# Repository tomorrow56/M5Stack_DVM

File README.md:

# M5Stack_DVM

M5Stackの内蔵ADCで作るアナログ電圧計です。
M5StackのWi-Fi機能を使って、内蔵A-Dコンバータで測定したデータを電圧に変換してGoogleスプレッドシートに記録するexampleを追加しました。

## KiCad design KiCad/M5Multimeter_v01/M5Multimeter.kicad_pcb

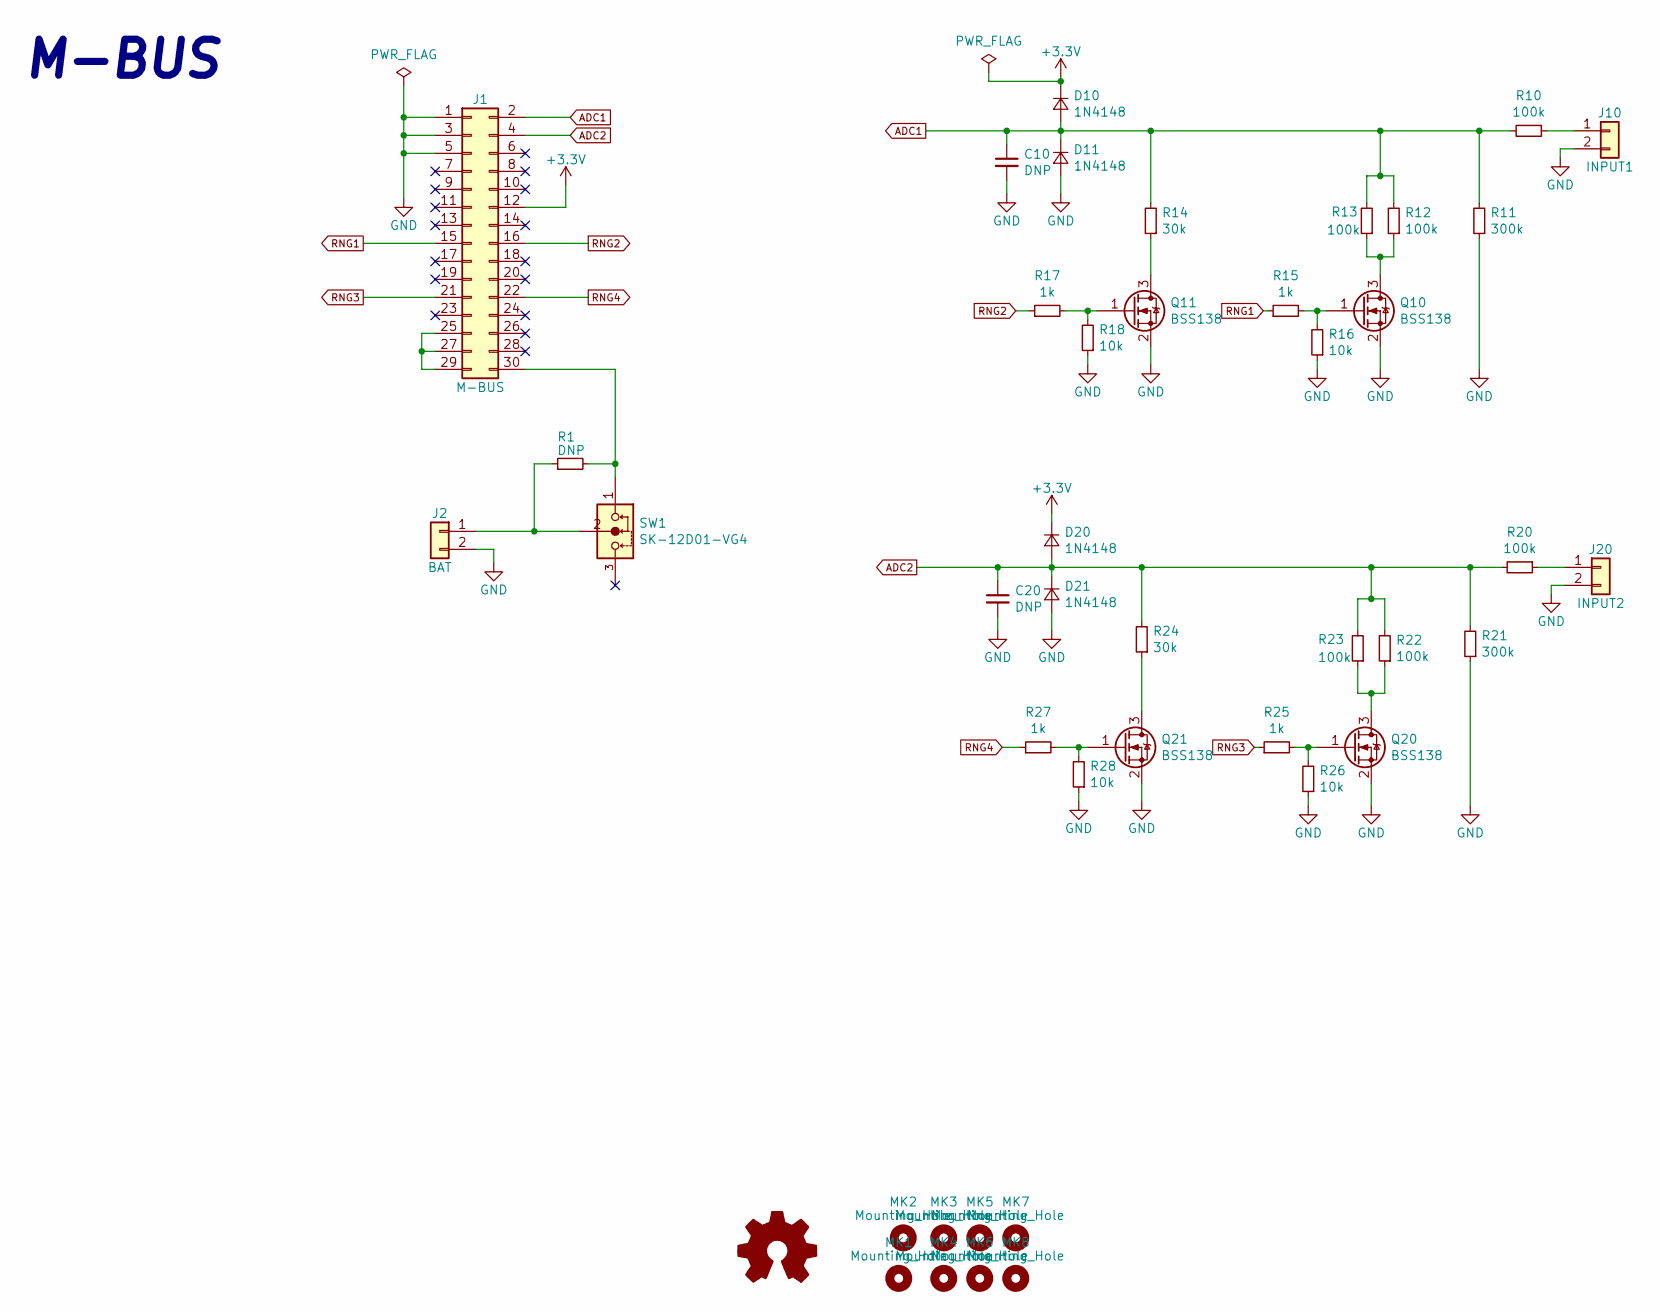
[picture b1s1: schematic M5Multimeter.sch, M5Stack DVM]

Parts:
C10, C20: DNP; C_0603
D10, D11, D20, D21: 1N4148; D_SOD-323
J1: M-BUS; Pin_Header_MBUS_SMD_TH
J2: BAT; Pin_Header_Angled_1x02_Pitch2.54mm
J10: INPUT1; Pin_Header_Angled_1x02_Pitch2.54mm
J20: INPUT2; Pin_Header_Angled_1x02_Pitch2.54mm
MK1, MK2, MK3, MK4: Mounting_Hole; MountingHole_3.2mm_M3
MK5, MK6, MK7, MK8: Mounting_Hole; MountingHole_2.2mm_M2
Q10, Q11, Q20, Q21: BSS138; SOT-23
R1: DNP; R_0603
R10, R12, R13, R20, R22, R23: 100k; R_0603
R11, R21: 300k; R_0603
R14, R24: 30k; R_0603
R15, R17, R25, R27: 1k; R_0603
R16, R18, R26, R28: 10k; R_0603
SW1: SK-12D01-VG4; slide_switch_angled

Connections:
+3V3: D10.1 (K), D20.1 (K), J1.12
ADC1: C10.1, D10.2 (A), D11.1 (K), J1.2, R10.2, R11.2, R12.2, R13.2, R14.2
ADC2: C20.1, D20.2 (A), D21.1 (K), J1.4, R20.2, R21.2, R22.2, R23.2, R24.2
GND: C10.2, C20.2, D11.2 (A), D21.2 (A), J1.1, J1.3, J1.5, J2.2, J10.2, J20.2, Q10.2 (S), Q11.2 (S), Q20.2 (S), Q21.2 (S), R11.1, R16.1, R18.1, R21.1, R26.1, R28.1
unnamed: J1.25, J1.27, J1.29
unnamed: J1.30, R1.2, SW1.1
unnamed: J2.1, R1.1, SW1.2
unnamed: J10.1, R10.1
unnamed: J20.1, R20.1
unnamed: Q10.1 (G), R15.2, R16.2
unnamed: Q10.3 (D), R12.1, R13.1
unnamed: Q11.1 (G), R17.2, R18.2
unnamed: Q11.3 (D), R14.1
unnamed: Q20.1 (G), R25.2, R26.2
unnamed: Q20.3 (D), R22.1, R23.1
unnamed: Q21.1 (G), R27.2, R28.2
unnamed: Q21.3 (D), R24.1
RNG1: J1.15, R15.1
RNG2: J1.16, R17.1
RNG3: J1.21, R25.1
RNG4: J1.22, R27.1

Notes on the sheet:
M-BUS

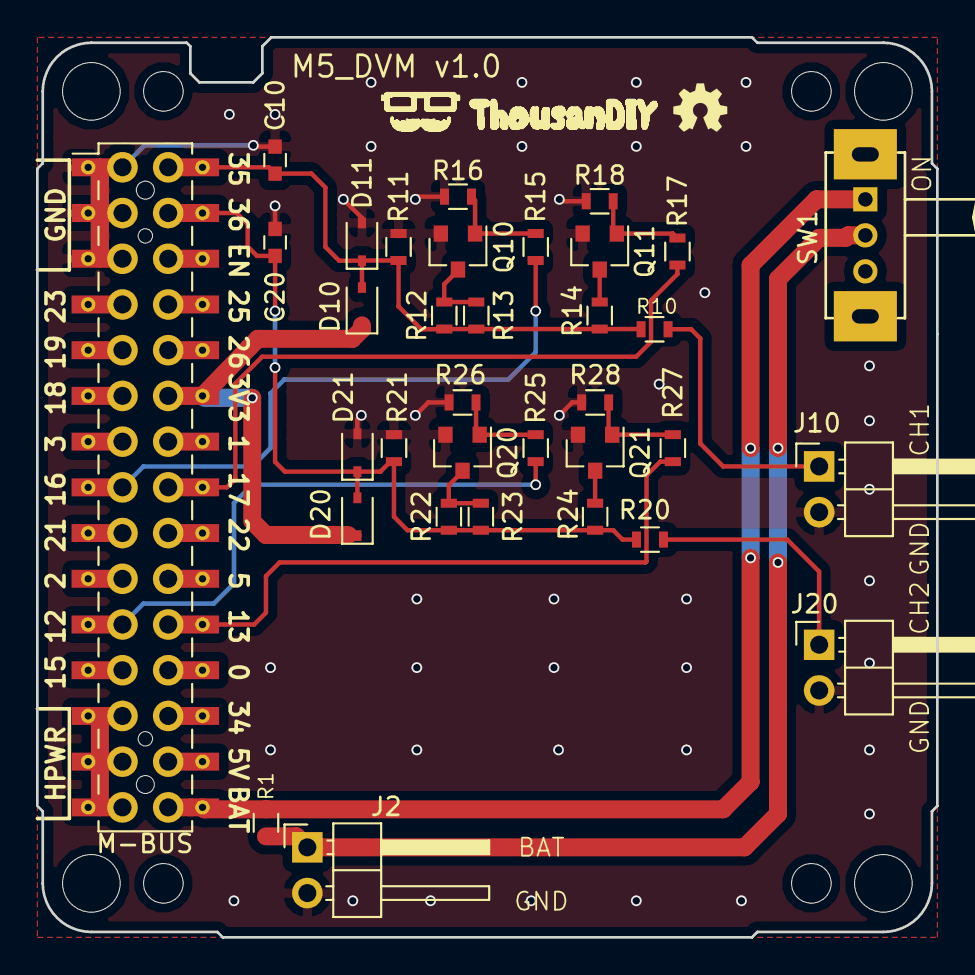
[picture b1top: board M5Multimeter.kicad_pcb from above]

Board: 2 copper layers, 50.0 x 50.0 mm, 43 parts (0 on the bottom side), 21 nets.

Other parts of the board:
ref**: val**; TDIY-LOGO-S

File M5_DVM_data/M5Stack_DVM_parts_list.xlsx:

M5Stack_DVK parts list
Name | Kind | Count | Catalog | Price [JPY] | URL
D10, D11, D20, D21 | Diode | 4 | 1N4148 | 100 | http://akizukidenshi.com/catalog/g/gI-07084/
Q10, Q11, Q20, Q21 | Transistor | 4 | BSS138 | 100 | http://akizukidenshi.com/catalog/g/gI-04232/
SW1 | Switch | 2 | SK-12D01-VG4 | 60 | http://akizukidenshi.com/catalog/g/gP-08789/
R15, R17, R25, R27 | Resistor 1k ohm | 4 | RK73B1JTTD102J | 218 | https://www.chip1stop.com/view/dispDetail/DispDetail?mpn=RK7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
R16, R18, R26, R28 | Resistor 10k ohm | 4 | RK73B1JTTD103J | 100 | https://www.chip1stop.com/view/dispDetail/DispDetail?mpn=RK7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
R14, R24 | Resistor 30k ohm | 2 | RK73B1JTTD303J | 134 | https://www.chip1stop.com/view/dispDetail/DispDetail?mpn=RK7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
R12, R13, R15, R22, R23, R25 | Resistor 100k ohm | 6 | RK73B1JTTD104J | 120 | https://www.chip1stop.com/view/dispDetail/DispDetail?mpn=RK7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
R11, R21 | Resistor 300k ohm | 2 | RK73B1JTTD304J | 100 | https://www.chip1stop.com/view/dispDetail/DispDetail?mpn=RK7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
C10, C20 | DNP (Do not Populate) | 0
R1 | DNP (Do not Populate) | 0
M5Stack |  | 1 |  | 3575 | https://www.switch-science.com/catalog/3647/
M5Stack Universal plate |  | 2 |  | 748 | https://www.switch-science.com/catalog/3650/

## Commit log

2019-01-20 Add schematic
2019-03-31 add PCB design data
2019-05-28 GND / VCC pattern correction
2019-09-01 probably a typo ?
2020-07-10 add parts list
    add parts list
2020-07-11 fix parts list
    fix parts list
2020-07-20 fix speaker noise
    fix speaker noise
    https://t-yosh.hatenablog.com/entry/2017/12/28/235947
2020-07-20 test for adding 2ch
    test for adding 2ch
2020-07-21 add photo for description(issue 1) is diode 1N4148 foot pattern more bit
    add photo for description(issue 1) is diode 1N4148 foot pattern more bit large
2020-07-22 added ch2, require code refactoring
    added ch2, require code refactoring
2020-07-26 configure A/D individual difference
    configure A/D individual difference
2020-08-12 add examples
2020-08-14 correct typo
2020-08-14 add WiFi setting message on LCD screen
